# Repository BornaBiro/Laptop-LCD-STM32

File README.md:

# Laptop-LCD-STM32
My little experiment trying to reuse old laptop LCD for some STM32 project.

# NOTE before proceeding!

This is just an experiment and that being said, use it on your own risk! I'm not guilty if you set your house on fire, hurt yourself (or someone else) or something like that.

# About the project
The main purpose of this project is to try to reuse old laptop LCD and drive it with STM32. The main reason behind this is to prove that reusing old LCD is not impossible nor it's complicated.

# Structure
- <u>**Docs**</u> - All documentation about this project
- <u>**FPGA**</u> - FPGA project code (used to convert RGB666/RGB565 into LVDS, more on that later)
- <u>**Hardware**</u> - Hardware related stuff (PCBs, Schematics, etc)
- <u>**STM32**</u> - Code for Nucleo-H743ZI2 board
- <u>**extras**</u> - All other stuff that are not strictly code related (images, notes etc)

### Docs
Self explanatory, documentation of this project. Need to add more stuff when I edit them.

### FPGA
All project files for the FPGA IDE. FPGA used in this project is [ULX3S board](https://www.crowdsupply.com/radiona/ulx3s). Board is based around Lattice ECP5 Series, LFE5U-12F-6BG381C. Used Toolchain is Lattice Diamond with Lattice LSE as main Synthesis tool. Used verion of the Lattice Diamond is 3.13. FPGA is not strictly neccessery here, everything can be replaced by one of these ICs [DS90C387, DS90CF388](https://www.ti.com/lit/ds/symlink/ds90cf388.pdf), [DS90C385A](https://www.ti.com/lit/ds/symlink/ds90c385a.pdf) or simmilar. But be careful on how to connect each RGB line of these ICs to the STM32. Follow LCD specifications on how bits are arranged inside the LVDS timeframe, not only the RGB to the LVDS IC datasheet! Main reason why I used FPGA instead of these dedicated ICs is flexibility - I can experiment with the pinout, I don't have to wait IC to arrive and I will learn something new while working with the FPGA. The whole FPGA code is written in Verilog.

### Hardware
For now, there is only KiCAD files for the custom LCD breakout board to be able to use original LCD cable for the laptop. I connector is salvaged from the laptop (removed from the laptop motherboard, it's not a easy job, I will say that) and soldered back again on my DIY PCB (I made this PCB using the toner transfer method). Connector seems to be BM40B-SRDS-G-TF but I'm not 100% sure. I was using KiCAD v8.0.

### STM32
STM32 is generating RGB565 signals for the LCD by using it's LTDC driver for color LCDs. Essentially, these RGB (LTDC) are encapsulated in LVDS. So LCD is actually getting RGB data signals. Main clock for this LCD is 50-70MHz. I choose 55MHz since everything above gives bad image quality due to absolutelly not ideal setup (just a note that main pixel clock is multiplied by the FPGA PLL 7 times to get one LVDS data line bit timeframe - 385MHz!). STM32 does not have enough memory for it to store whole LCD content - framebuffer. It's only displaying rectangle of 354*354 by using one of the LTDC layers. Why I chose this resolution - I have no idea. By making custom board, SDRAM can be attached to the STM32 where whole frame buffer can be stored and in that case, some graphical engine can be added (LVGL comes to my mind as well as Adafruit GFX). STM32 code is written in STM32CubeIDE and images are generated by the LCD image converter, RGB565 preset, 16bit packing. Note that STM32 LTDC has it's limitations on max pixel clock (75MHz in this case) and these LCDs have minimal pixel clock (in this case 50 MHz).

### LCD
Yep, the star of the show! My LCD has a part number B154EW02-V2 by AUO. It's from old HP 6735b laptop. It's resolution is 1280x800, with 18 bit color? You can find datasheet on the web, but if needed, I can publish it here. Main issues were:

- LCD Connector pinout (easy, datasheet) and LCD cable pinout (harder, reverse eng.)
- LCD inverter pinout - yes, this is old-school LCD with CCFL and inverter is needed. Luckly, I have an original LCD inverter from the laptop, again pinout is missing. Little bit more reverse eng. and the pinout and working principle are known. I will post pinout for both LCD cable and LCD inverter as soon as possible.
<u>**NOTE**: LCD inverters are working with very high voltages >5kV, this can shock you or burn you! Be aware!</u>
- LCD bit arrangement inside LVDS time-frames - Again datasheet is your friend. If the datasheet is missing and LCD uses only 3 LVDS lines, can only be one of two standards; VESA and JEDIA (see potato image below that I found on the web). My LCD uses 6 bit color VESA standard. Trial and error method is your friend.

## Known issues
- Random green and red pixels - Due bad FPGA input voltage standards. It should use LVCMOS3V3 for all RGB input, but due my bad pinout arragment, this is not possible for all pins, so all pins are switshed to the LVCMOS2V5 and that causes some noise that traslates into wrong pixels being light up. For the green, this can be reduced to some exted by using 330R pull-down on MSB on the green color. I need to do this better.
- Image full of noise and jitter - Switch STM32 to use XTAL as reference clock for the PLL for the LTDC. For some reason, HSI and MSI are very noisy and PLL inside FPGA amplify that noise and jitter and we get very unstable image on the screen. Using HSE at reference source for the STM32 PLL fixed the issue.
- No full frame buffer - this one is not easy to fix, custom STM32 board with fast SDRAM is needed, maybe I make one. 

## How to reuse this on my LCD?
First, you need to find the resolution of your LCD. This should be easy. This is important to be able to calculate pixel clock. W * H * frameRate ~ Pixel Clock. In this case: 1280 * 800 * 50Hz = 51.2MHz. This is only rugh estimation, pixel clock is little bit higher due vertical and horizontal blanking intervals. Next, you need to find out the pinout for the LCD. In fact, the best thing is to get the datasheet of the LCD. There are two ways for this; google the part number of the LCD or open LCD and try to find the datasheet of the LCD controller. **BUT** be careful not to damage the LCD!

Now when you have the pinout, you need to connect the LCD to the FPGA or somekind of breakout board. I salvaged original LCD cable from the laptop and the connector from the laptop motherborad *_(hint - if you don't want to melt the connector while unsoldering, heat the board from the opposite side of the conncetor)_*. I made a [custom PCB]() as a adapter for the cable in KiCad and made PCB at home.

Now you need to find out the pinout of the cable itself. By using multimeter and continuity function, put one probe on the LCD side of the connector and other one at the PCB adapter. Go one-by-one pin at the custom board until you hear the _*beep*_. You don't need go though all this trouble, you can just buy a LCD connector and solder the wires on it, or just a cut original LCD cable (motherboard side of course). But I wanted to make it the _*"right way"*_.

## Using exactly this LCD and this repo.
1. Get the ULX3S board
2. Get the Nucleo-H743ZI2 board
3. Get the Lattice Diamond and install it
4. Get the STM32CubeIDE and STM32H7 firmware package and install it both
5. Sythesis the Verilog code and upload the .bit file to the UXL3S board. I used [fujiprog](https://github.com/kost/fujprog). For Win machine I needed to install FTDI Drivers and Zadig (follow [this](https://github.com/kost/fujprog?tab=readme-ov-file#windows-drivers) for more info).
6. Build and upload code to the STM32 board.
7. Connect everything using [this diagram](https://github.com/BornaBiro/Laptop-LCD-STM32/blob/master/Docs/LCD_Timings_And_Connections.txt)
8. Power everything up. With a little luck, there should not be any smoke, but instead image will be shown on the screen.

All diagrams (txt) for the LCD can be found [here](https://github.com/BornaBiro/Laptop-LCD-STM32/tree/master/Docs).

Power supply: You can use USB on STM32 and ULX3S boards for the supply, only LCD Inverter (backlight) is using 9V-12V, **BUT** EN and DRBT pins of the LCD inverter are 3V3!

## I have a XY LCD, can you write the code for me?
Nope. I think that I gave you enough info to get you started. If I missed something, please let me know, I will try my best to fill in the gaps.

## To-DO
- Use graphics instead of the txt files for connections
- Better LVDS module for FPGA
- Custom STM32 PCB with SDRAM and dedicated RGB -> LVDS IC
- Change the name of the FPGA project to something different than "blink" 🤦

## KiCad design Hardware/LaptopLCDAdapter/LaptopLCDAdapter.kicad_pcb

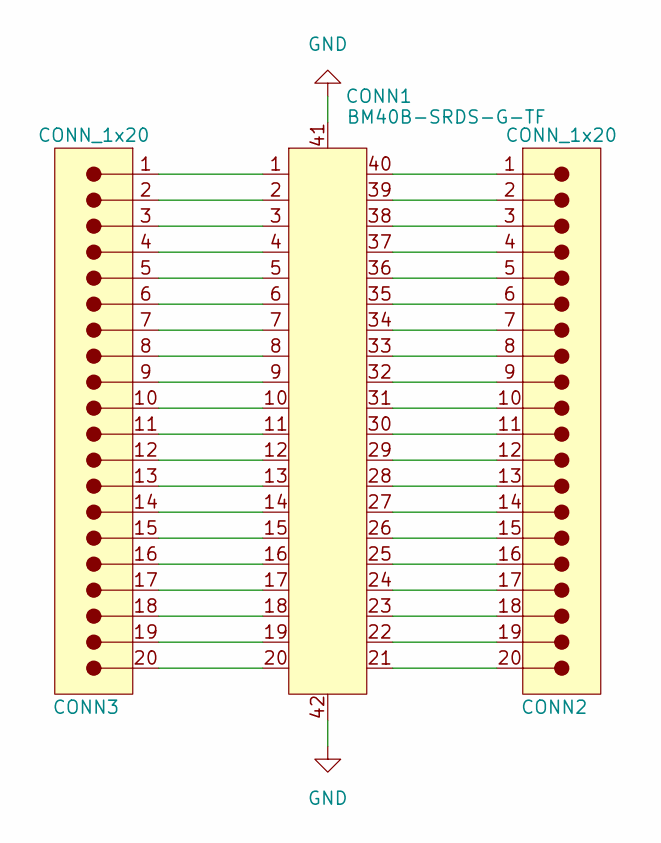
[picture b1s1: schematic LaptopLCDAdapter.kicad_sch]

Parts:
CONN1: BM40B-SRDS-G-TF
CONN2, CONN3: CONN_1x20; CONN1X20

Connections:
GND: CONN1.41, CONN1.42
unnamed: CONN1.1, CONN3.1
unnamed: CONN1.2, CONN3.2
unnamed: CONN1.3, CONN3.3
unnamed: CONN1.4, CONN3.4
unnamed: CONN1.5, CONN3.5
unnamed: CONN1.6, CONN3.6
unnamed: CONN1.7, CONN3.7
unnamed: CONN1.8, CONN3.8
unnamed: CONN1.9, CONN3.9
unnamed: CONN1.10, CONN3.10
unnamed: CONN1.11, CONN3.11
unnamed: CONN1.12, CONN3.12
unnamed: CONN1.13, CONN3.13
unnamed: CONN1.14, CONN3.14
unnamed: CONN1.15, CONN3.15
unnamed: CONN1.16, CONN3.16
unnamed: CONN1.17, CONN3.17
unnamed: CONN1.18, CONN3.18
unnamed: CONN1.19, CONN3.19
unnamed: CONN1.20, CONN3.20
unnamed: CONN1.21, CONN2.20
unnamed: CONN1.22, CONN2.19
unnamed: CONN1.23, CONN2.18
unnamed: CONN1.24, CONN2.17
unnamed: CONN1.25, CONN2.16
unnamed: CONN1.26, CONN2.15
unnamed: CONN1.27, CONN2.14
unnamed: CONN1.28, CONN2.13
unnamed: CONN1.29, CONN2.12
unnamed: CONN1.30, CONN2.11
unnamed: CONN1.31, CONN2.10
unnamed: CONN1.32, CONN2.9
unnamed: CONN1.33, CONN2.8
unnamed: CONN1.34, CONN2.7
unnamed: CONN1.35, CONN2.6
unnamed: CONN1.36, CONN2.5
unnamed: CONN1.37, CONN2.4
unnamed: CONN1.38, CONN2.3
unnamed: CONN1.39, CONN2.2
unnamed: CONN1.40, CONN2.1

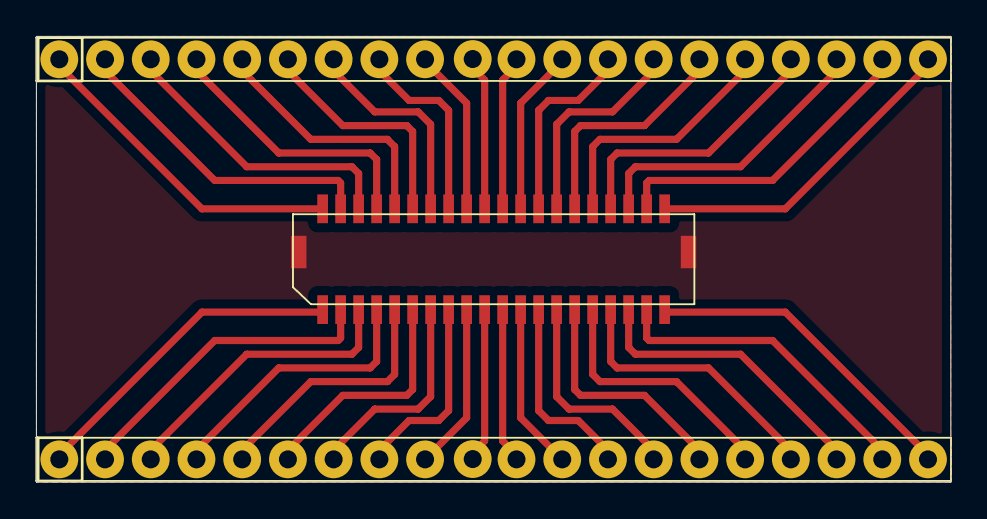
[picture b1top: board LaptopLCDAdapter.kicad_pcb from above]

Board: 2 copper layers, 50.8 x 24.8 mm, 3 parts (0 on the bottom side), 41 nets.

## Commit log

2024-07-15 Added all files (maybe I need to do a lot of clean-up).
    Let's just say the LCD is showing one color without the flicker.
2024-07-15 Added ability to change screen colors with DIP switches.
2024-07-15 Lattice Diamond IDE files update?
2024-07-16 FPGA is now converting RGB to LVDS (only 8 bit RGB323).
2024-07-16 Fixed FPGA RGB to LVDS converter, STM32 is now outputs an "image" to the LCD.
    FPGA: Blocking and non-blocking expressions issue.
    STM32: Buffer window size and position issue.
2024-07-17 Image finally displayed on the screen from the STM32.
2024-07-21 Partially fixed LCD issues - Green pixels are due voltage incompatibility between STM32 and FPGA.
    Setting everything to 2V5 inputs on FPGA with pull-ups or without pull-ups or pull-downs and adding 330R pull-down resistor on G5 (G7 STM32) line improved image quality.
    To-Do: Better GPIO management on FPGA side to support 3V3 inputs as well as LVDS.
2024-07-22 Added documentation, readme.
2024-07-28 More documentation stuff!
2024-07-28 Added PCB.
